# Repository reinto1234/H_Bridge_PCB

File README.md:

# H-Bridge PCB Project

## Project Description
This project involves the design and implementation of an **educational single-phase H-Bridge inverter** controlled by an **Espressif ESP32**.  
The system demonstrates **bipolar sinusoidal PWM (SPWM)** operation with **closed-loop VRMS amplitude control** and a **browser-based interface** for monitoring and control.  
The H-Bridge can drive loads with the following ratings:

- **Input Voltage:** 24 V  
- **Input Current:** up to 10 A  
- **Power:** ≈ 240 W  

### Features
- Fixed **switching frequency:** 35 kHz  
- Fixed **output frequency:** 50 Hz  
- **Bipolar SPWM modulation** (only)  
- **Closed-loop VRMS control** using PI regulation  
- **Web-based UI** (HTTP + WebSocket) for control and telemetry  
- **Input/Output power measurement**  
- **Overcurrent protection** using INA228 (auto driver shutdown + UI fault latch)  

The project consists of two main components:  
1. **H_Bridge_PCB_Design** — KiCad PCB layout and schematic.  
2. **H_Bridge_PCB_Code** — Firmware for the ESP32 controller.

---

## Directory Structure

<h2>Directory Structure</h2>
<pre><code>H_Bridge_PCB_Project/
├── H_Bridge_PCB_Design/        # KiCad design files
├── H_Bridge_PCB_Code/          # ESP32 firmware
│   ├── include/                # Header files
│   │   ├── Controller.h
│   │   ├── I2C.h
│   │   ├── Input_meas.h
│   │   ├── mutexdefinitions.h
│   │   ├── Output_meas.h
│   │   ├── PWM.h
│   │   ├── spi_sampler.h
│   │   ├── Tasks.h
│   │   └── webserver.h
│   │
│   ├── src/                    # Source files
│   │   ├── Controller.cpp
│   │   ├── I2C.cpp
│   │   ├── Input_meas.cpp
│   │   ├── Output_meas.cpp
│   │   ├── PWM.cpp
│   │   ├── spi_sampler.cpp
│   │   ├── Tasks.cpp
│   │   ├── webserver.cpp
│   │   └── main.cpp
│   │
│   ├── data/                   # Webserver files (LittleFS)
│   │   ├── index.html
│   │   ├── script.js
│   │   └── style.css
│
├── lib/                        # Optional local libraries
├── platformio.ini              # PlatformIO configuration
├── images/                     # Flowchart and figures
└── README.md                   # This file
</code></pre>

---

## Requirements

### Hardware:
- PCB based on KiCad design  
- 24 V DC power supply (≥ 10 A)  
- Resistive or inductive load (max ≈ 240 W)  
- Gate drivers with integrated dead-time  
- INA228 current/voltage monitor for input sensing  

### Software:
- [KiCad](https://www.kicad.org/) — PCB design  
- [PlatformIO](https://platformio.org/) — firmware build  
- [VS Code](https://code.visualstudio.com/) — recommended IDE  

---

## Webserver
The ESP32 provides a **built-in Wi-Fi access point** and hosts a **web-based interface** for control and measurement visualization.

### Connect to WLAN Access Point
- **SSID:** `H_Bridge_Control`  
- **Password:** `12345678`

### Open the web interface:
👉 [http://192.168.4.1/](http://192.168.4.1/)

**Functions:**
- Start/Stop the inverter  
- Set VRMS target  
- Display live telemetry (Vin, Iin, VRMS, IRMS, PF, P, Q, f)  
- View and acknowledge overcurrent faults  

---

## Code
The firmware is implemented in **C++** (Arduino / FreeRTOS).  
The web interface is built with **HTML**, **JavaScript**, and **CSS**.

---

### Flowchart

---

## Code Documentation
Brief overview of the most relevant components.

### Inverter Implementation (`PWM.cpp`)
Implements the real-time control of the full-bridge inverter:

- **startInverter()** — Initializes and enables PWM output.  
- **stopInverter()** — Stops PWM and resets inverter state.  
- **generateSPWM()** — Produces bipolar SPWM using a sine table.  
- **begin()** — Configures LEDC channels, frequency, and timers.  
- **getMeasurements()** — Retrieves latest measurement snapshot.  
- **computePI()** — Executes PI algorithm to maintain VRMS target.  
- **loop()** — Runs the inverter control logic at fixed timing intervals.  

### Controller Implementation (`Controller.cpp`)
Implements the PI controller used to regulate the inverter’s RMS output voltage:

- **PIController()** — Initializes PI gains, integrator state, limits, and VRMS target.  
- **ControlRMS()** — Computes RMS error and updates the global Q10 amplitude factor atomically.  
- **compute()** — Executes PI algorithm with anti-windup and output clamping to min/max limits.  
- **g_amp_q10** — Global Q10-formatted amplitude value used by the SPWM stage.  

### I²C Bus Setup (`I2C.cpp`)
Implements the I²C interface for the INA228 current/voltage sensor:

- **I2CINA** — Dedicated I²C bus instance (port 0) used by the input measurement subsystem.  

### Input Measurement (`Input_meas.cpp`)
Implements DC input voltage, current, and power measurement using INA228:

- **init()** — Initializes I²C bus, scans for devices, configures INA228, and sets averaging/timing.  
- **init1()** — Lightweight I²C initialization helper without full sensor setup.  
- **configure_overcurrent_alert_only()** — Configures INA228 alert registers for shunt overcurrent shutdown.  
- **getVoltage()** — Reads and returns the DC input voltage in volts.  
- **getCurrent()** — Reads and returns the shunt current in amperes.  
- **getPower()** — Reads and returns the input power in watts with simple error rejection.  
- **measurementall()** — Updates the shared input measurement buffer (voltage, current, power) in a mutex-protected way and returns it.  
- **scanI2C()** — Scans the I²C bus, prints found devices, and restarts the bus if no device is detected.  

### Main Application (`main.cpp`)
Implements system bring-up and FreeRTOS task orchestration:

- **setup()** — Initializes serial logging, mutexes, input measurement, Wi-Fi AP, webserver, SPI measurement engines, safety pins, and the overcurrent interrupt; then creates all application tasks.  
- **loop()** — Empty main loop; periodically yields since all logic is implemented in FreeRTOS tasks.  
- **Task handles** — Stores references to sampler, analyzer, WebSocket, controller, printer, and emergency stop tasks for debugging/management.  

### Mutex Definitions (`mutexdefinitions.cpp`)
Implements globally shared FreeRTOS mutexes for synchronization:

- **inverterMutex** — Protects access to the inverter state and control functions.  
- **measurementinMutex** — Protects shared input measurement buffer.  
- **measurementoutMutex** — Protects shared output measurement structures.  
- **measurementSpiMutex** — Protects SPI-related measurement buffers and state.  

### Output Measurement (`Output_meas.cpp`)
Implements decimation, CIC filtering, RMS, and frequency analysis for AMC1306 bitstreams:

- **buildByteCicLut()** — Precomputes CIC integrator/differentiator contributions for all 8-bit patterns.  
- **OutputMeasurements()** — Configures OSR, full-scale voltage, buffer sizes, and initial bit rate.  
- **init()** — Allocates decimation ring buffers, analysis windows, and period buffers (with PSRAM support) and creates a snapshot mutex.  
- **copyRecentWindowWithStats()** — Copies the newest segment from the decimation ring and computes mean, min, and max.  
- **findLastTwoRisingZcHyst()** — Detects the last two rising zero-crossings with hysteresis to define one AC period.  
- **computeRmsOnePeriodExact()** — Computes exact RMS over one period using piecewise linear interpolation.  
- **processRxBytesAndUpdateBitrate()** — Processes raw SPI bytes, runs CIC pipeline, generates decimated voltage samples, and updates effective bit rate.  
- **analyzeStep()** — Centers the signal, finds period boundaries, computes frequency, extracts a centered period, and calculates RMS.  
- **getSnapshot()** — Returns the latest snapshot (RMS, frequency, period length) in a thread-safe way.  
- **copyLastPeriod()** — Copies the last detected waveform period into a caller-provided buffer.  
- **copySinceSeq32()** — Provides incremental decimated samples since a given sequence index, for streaming or plotting.  

### Emergency Stop (`safety.cpp`)
Implements minimal emergency-stop signaling for overcurrent events:

- **g_emergency_stop** — Global volatile flag indicating an active emergency stop condition.  
- **onAlertISR()** — ISR that sets the emergency stop flag when the INA228 alert pin fires.  

### SPI Sampler (`spi_sampler.cpp`)
Implements DMA-driven SPI acquisition for dual AMC1306 isolated ADC channels:

- **g_ch1_om / g_ch2_om** — OutputMeasurements instances for both channels with hardware-specific scaling.  
- **g_sampler1 / g_sampler2** — Sampler context structures for SPI hosts, pins, DMA channels, and transactions.  
- **g_pack1 / g_pack2** — Pairs of sampler context and OutputMeasurements used by sampler tasks.  
- **spiSamplerInitMeasurements()** — Initializes both OutputMeasurements engines and validates buffer allocation.  
- **spiInitAndStart()** — Allocates DMA buffers, configures SPI bus and device, prepares transactions, and seeds the transaction queue.  

### Task Scheduler (`Tasks.cpp`)
Implements all FreeRTOS tasks for sampling, analysis, UI updates, control, and safety:

- **spiSamplerTask()** — Retrieves completed SPI DMA transactions, feeds data into OutputMeasurements, requeues transactions, and maintains sampling timing.  
- **analyzerTask()** — Periodically calls analyzeStep() on a given OutputMeasurements instance to update RMS and frequency.  
- **printerTask()** — Periodically prints analyzer timing, latest period samples, RMS, and frequency for both channels over serial.  
- **webSocketTask()** — Processes WebSocket events in a loop to keep client connections responsive.  
- **webSocketUpdate()** — Periodically collects input and output measurements and sends them as JSON via WebSocket to the UI.  
- **ControllerTask()** — Runs the VRMS control loop by feeding the measured RMS value into the PI controller of the inverter.  
- **EmergencyStopTask()** — Monitors the global emergency-stop flag, stops the inverter, signals the E-STOP output, and notifies the web UI when overcurrent is detected.  

### Webserver (`webserver.cpp`)
Implements Wi-Fi access point, HTTP endpoints, and WebSocket telemetry/UI control:

- **resetDefaults()** — Resets VRMS target and running state to their default values.  
- **initWiFi()** — Starts the Wi-Fi SoftAP for the H-Bridge control interface.  
- **initServer()** — Mounts LittleFS, serves static `/index.html`, `/style.css`, `/script.js`, and defines `/start`, `/stop`, and `/ack-trip` endpoints.  
- **updateMeasurements()** — Packs input/output data and frequency into JSON and broadcasts it over WebSocket.  
- **broadcastStatus()** — Sends current inverter running state to all connected clients via WebSocket.  
- **onWebSocketEvent()** — Handles client connect/disconnect events and sends initial status on connect.  
- **broadcastTrip()** — Notifies all clients of a trip condition and updates running state.  
- **_VRMS / _isRunning** — Static internal state for desired RMS value and inverter run/stop status.  

**HTTP Endpoints:**
- `/` – Main HTML page  
- `/start` – Start inverter  
- `/stop` – Stop inverter  
- `/update` – Update VRMS target  
- `/bipolar.png` – Waveform reference  

---

## Overcurrent Protection
Overcurrent protection is implemented through the **INA228** fault pin:  
1. When a current threshold is exceeded, **drivers are disabled immediately**.  
2. A **fault message** is sent to the web interface.  
3. After user acknowledgment, the inverter can be restarted safely.  

---

## Safety  
- Use **current-limited** power supplies during development.  
- Verify **MOSFET temperature and load** ratings.  
- For **educational/laboratory use only**.

---

## License
Released for **educational and research purposes**.  
Use responsibly.

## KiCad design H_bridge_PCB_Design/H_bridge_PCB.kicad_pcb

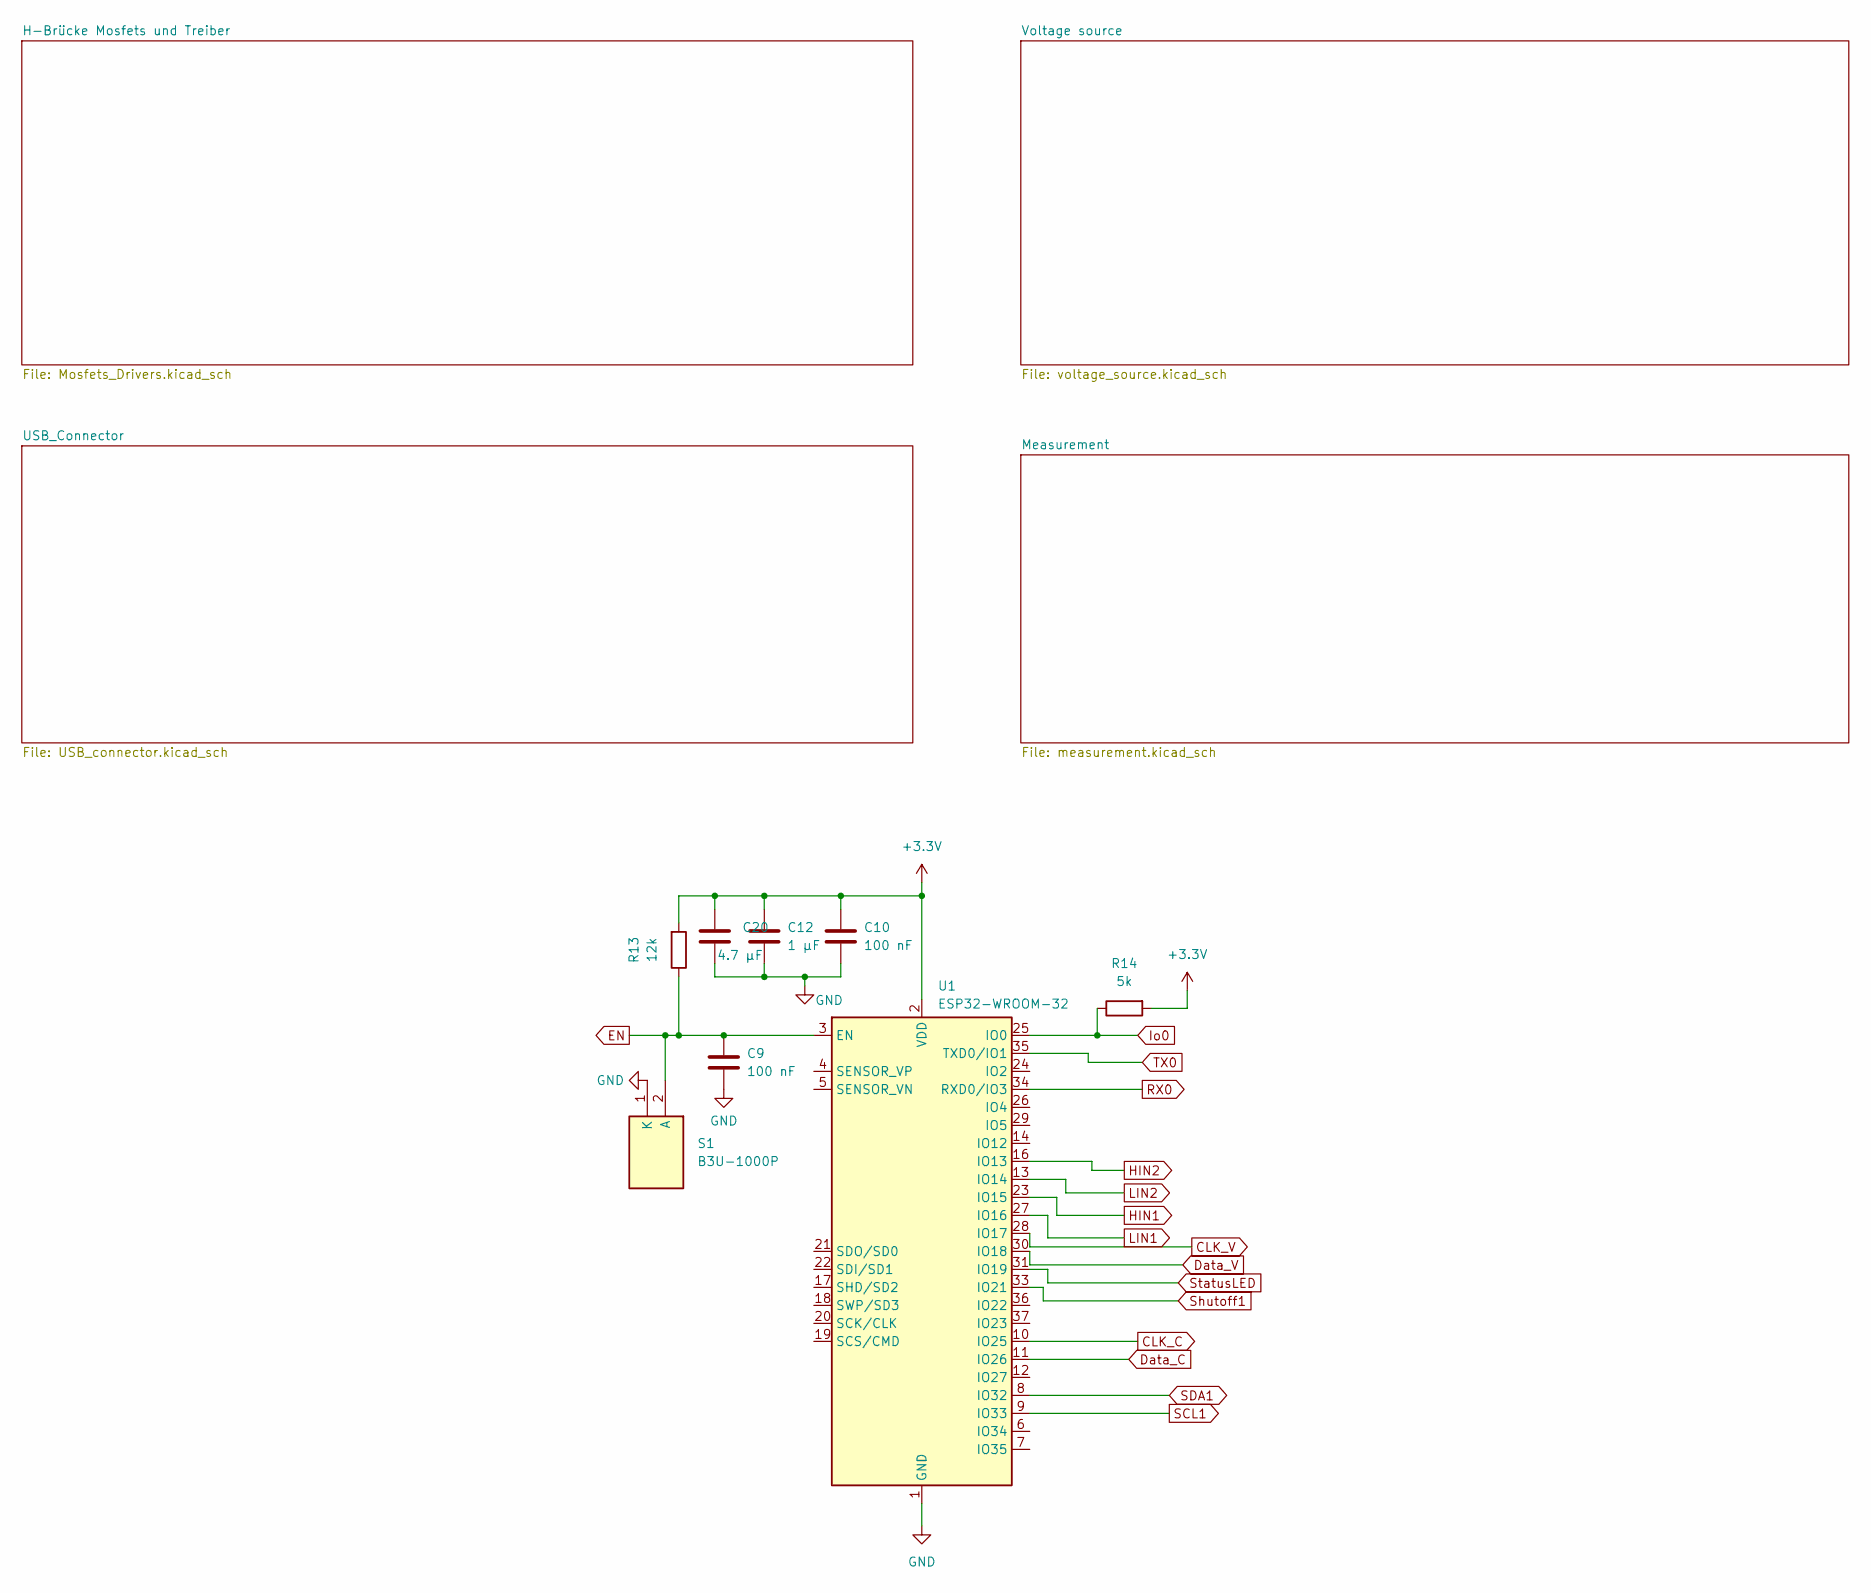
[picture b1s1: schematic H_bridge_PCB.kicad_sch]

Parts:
C9, C10: 100 nF; R_0805_2012Metric_Pad1.20x1.40mm_HandSolder; LCSC Part # C49678
C12: 1 µF; R_0805_2012Metric_Pad1.20x1.40mm_HandSolder; LCSC Part # C28323
C20: 4.7 µF; R_0805_2012Metric_Pad1.20x1.40mm_HandSolder; LCSC Part # C49678
R13: 12k; R_0805_2012Metric_Pad1.20x1.40mm_HandSolder; LCSC Part # C139925
R14: 5k; R_0805_2012Metric_Pad1.20x1.40mm_HandSolder; LCSC Part # C2828700
S1: B3U-1000P; Manufacturer_Part_Number B3U-1000P; Mouser Part Number 653-B3U-1000P
U1: ESP32-WROOM-32; LCSC Part # C701343

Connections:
+3.3V: C10.1, C12.1, C20.1, R13.2, R14.2, U1.2 (VDD); also elsewhere on the board
CLK_C: U1.10 (IO25); also elsewhere on the board
CLK_V: U1.28 (IO17); also elsewhere on the board
Data_C: U1.11 (IO26); also elsewhere on the board
Data_V: U1.30 (IO18); also elsewhere on the board
EN: C9.1, R13.1, S1.2 (A), U1.3 (EN); also elsewhere on the board
GND: C9.2, C10.2, C12.2, C20.2, S1.1 (K), U1.1 (GND), U1.15 (GND), U1.38 (GND), U1.39 (GND); also elsewhere on the board
HIN1: U1.23 (IO15); also elsewhere on the board
HIN2: U1.16 (IO13); also elsewhere on the board
Io0: R14.1, U1.25 (IO0); also elsewhere on the board
LIN1: U1.27 (IO16); also elsewhere on the board
LIN2: U1.13 (IO14); also elsewhere on the board
RX0: U1.34 (RXD0/IO3); also elsewhere on the board
SCL1: U1.9 (IO33); also elsewhere on the board
SDA1: U1.8 (IO32); also elsewhere on the board
Shutoff1: U1.33 (IO21); also elsewhere on the board
StatusLED: U1.31 (IO19)
TX0: U1.35 (TXD0/IO1); also elsewhere on the board

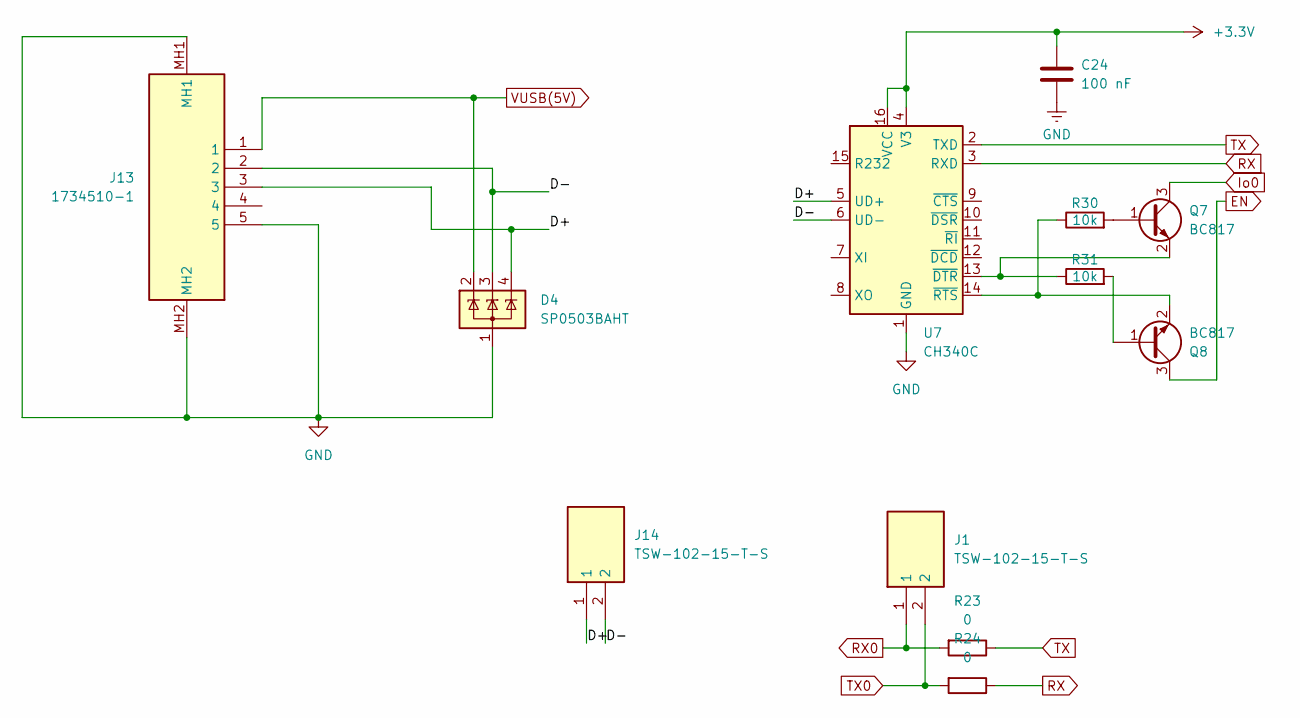
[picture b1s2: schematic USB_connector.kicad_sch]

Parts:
C24: 100 nF; R_0805_2012Metric_Pad1.20x1.40mm_HandSolder; LCSC Part # C49678
D4: SP0503BAHT; SOT-143; LCSC Part # C7074
J1, J14: TSW-102-15-T-S; TSW-102-XX-YY-S; Mouser Part Number 200-TSW10215TS
J13: 1734510-1; 17345101; Mouser Part Number 571-1734510-1
Q7, Q8: BC817; SOT-23_Handsoldering; LCSC Part # C475629
R23, R24: 0; R_0805_2012Metric_Pad1.20x1.40mm_HandSolder; LCSC Part # C2074219
R30, R31: 10k; R_0805_2012Metric_Pad1.20x1.40mm_HandSolder; LCSC Part # C84376
U7: CH340C; SOIC-16_3.9x9.9mm_P1.27mm; LCSC Part # C84681

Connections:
+3.3V: C24.1, U7.4 (V3), U7.16 (VCC); also elsewhere on the board
/USB_Connector/D+: D4.4 (K), J13.3, J14.1, U7.5 (UD+)
/USB_Connector/D-: D4.3 (K), J13.2, J14.2, U7.6 (UD-)
EN: Q8.3 (C); also elsewhere on the board
GND: C24.2, D4.1 (A), J13.5, J13.MH1, J13.MH2, U7.1 (GND); also elsewhere on the board
Io0: Q7.3 (C); also elsewhere on the board
unnamed: Q7.1 (B), R30.2
unnamed: Q7.2 (E), R31.1, U7.13 (~DTR)
unnamed: Q8.1 (B), R31.2
unnamed: Q8.2 (E), R30.1, U7.14 (~RTS)
RX: R24.1, U7.3 (RXD)
RX0: J1.1, R23.2; also elsewhere on the board
TX: R23.1, U7.2 (TXD)
TX0: J1.2, R24.2; also elsewhere on the board
VUSB(5V): D4.2 (K), J13.1; also elsewhere on the board

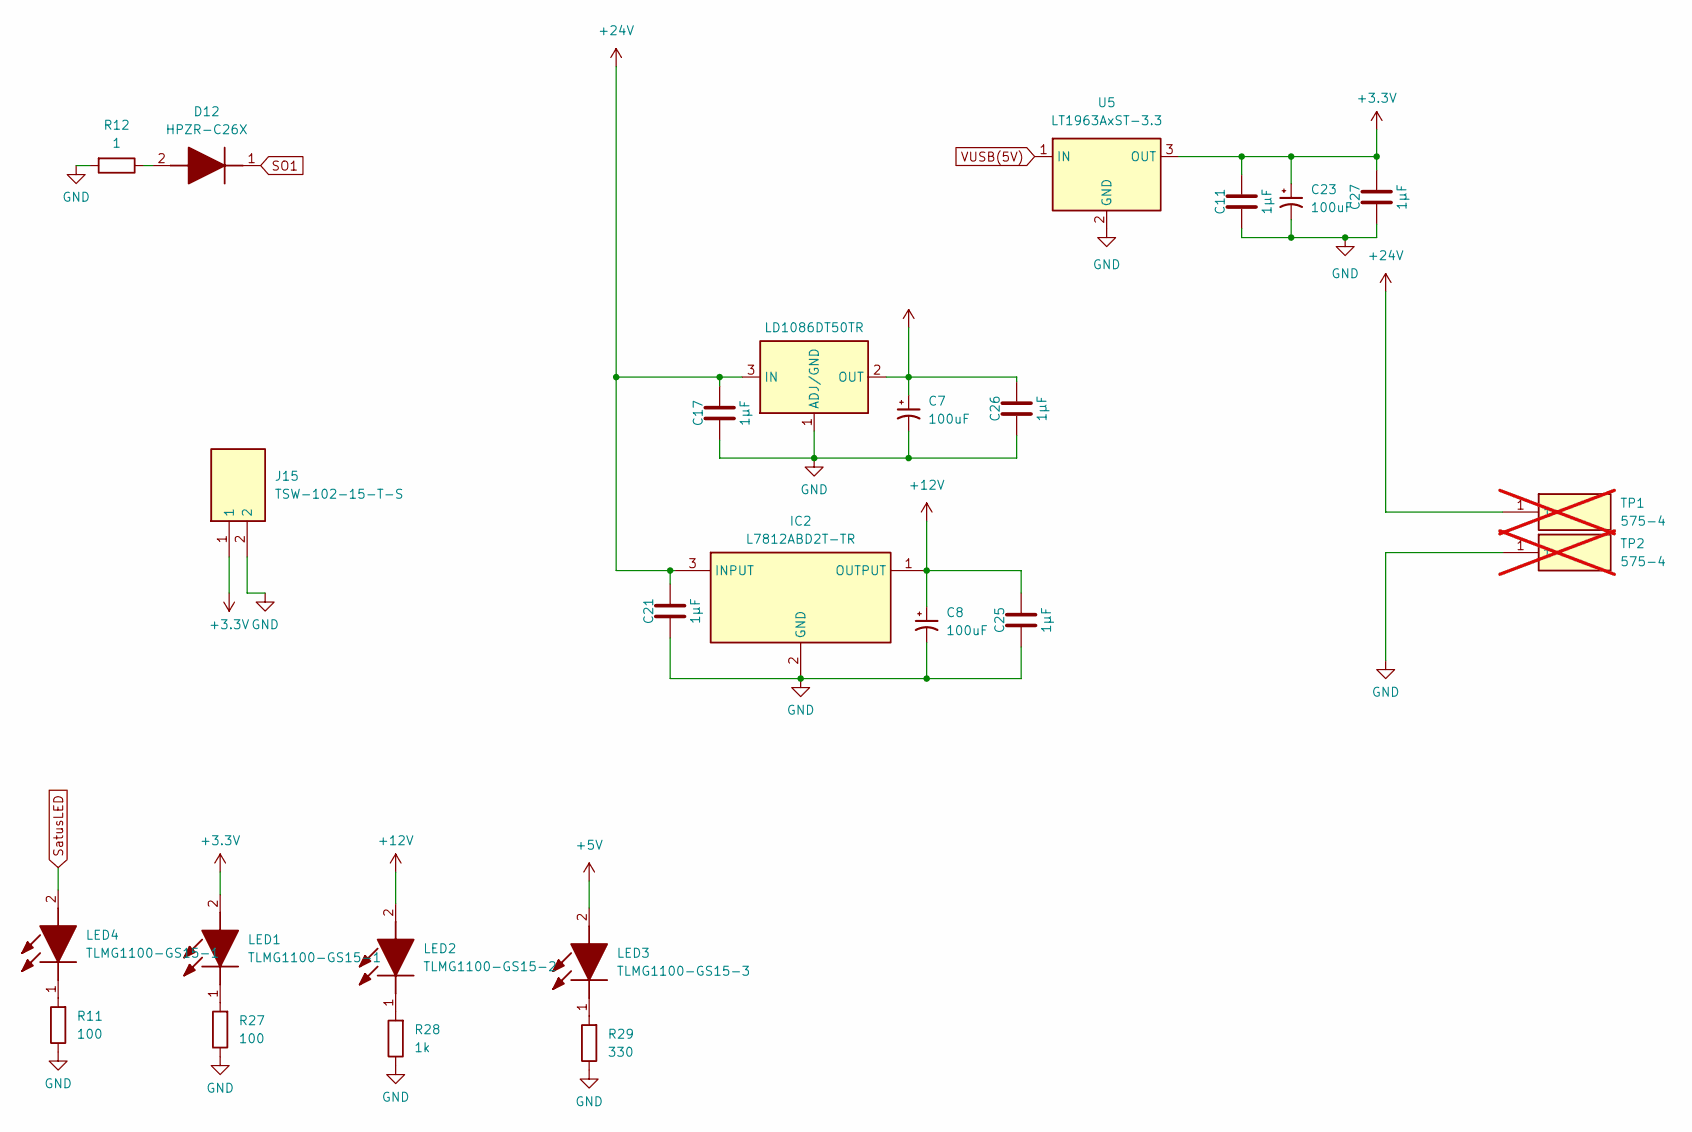
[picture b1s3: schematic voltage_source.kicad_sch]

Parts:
C7, C8, C23: 100uF; EEE1AA101SP; LCSC Part # C128464
C11, C17, C21, C25, C26, C27: 1µF; R_0805_2012Metric_Pad1.20x1.40mm_HandSolder; LCSC Part # C28323
D12: HPZR-C26X; HPZRC26X; Manufacturer_Part_Number HPZR-C26X
IC2: L7812ABD2T-TR; L7812ABD2TTR; Manufacturer_Part_Number L7812ABD2T-TR; Mouser Part Number 511-L7812ABD2T-TR
J15: TSW-102-15-T-S; TSW-102-XX-YY-S; Mouser Part Number 200-TSW10215TS
LED1, LED4: TLMG1100-GS15-1; R_0805_2012Metric_Pad1.20x1.40mm_HandSolder; Mouser Part Number 78-TLMG1100-GS15
LED2: TLMG1100-GS15-2; R_0805_2012Metric_Pad1.20x1.40mm_HandSolder; Mouser Part Number 78-TLMG1100-GS15
LED3: TLMG1100-GS15-3; R_0805_2012Metric_Pad1.20x1.40mm_HandSolder; Mouser Part Number 78-TLMG1100-GS15
R11, R27: 100; R_0805_2012Metric_Pad1.20x1.40mm_HandSolder; LCSC Part # C115423
R12: 1; R_0805_2012Metric_Pad1.20x1.40mm_HandSolder; LCSC Part # C4129769
R28: 1k; R_0805_2012Metric_Pad1.20x1.40mm_HandSolder; LCSC Part # C95781
R29: 330; R_0805_2012Metric_Pad1.20x1.40mm_HandSolder; LCSC Part # C4129769
TP1, TP2: 575-4; 5754; Mouser Part Number 534-575-4; not fitted
U5: LT1963AxST-3.3; SOT-223-3_TabPin2; LCSC Part # C459918
U6: LD1086DT50TR; TO-252-2; LCSC Part # C164853

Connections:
+3.3V: C11.1, C23.1, C27.1, J15.1, LED1.2 (A), U5.3 (OUT); also elsewhere on the board
+5V: C7.1, C26.1, LED3.2 (A), U6.2 (OUT); also elsewhere on the board
+12V: C8.1, C25.1, IC2.1 (OUTPUT), LED2.2 (A); also elsewhere on the board
GND: C7.2, C8.2, C11.2, C17.2, C21.2, C23.2, C25.2, C26.2, C27.2, IC2.2 (GND), J15.2, R11.1, R12.2, R27.1, R28.1, R29.1, TP2.1, U5.2 (GND), U6.1 (ADJ/GND); also elsewhere on the board
unnamed: D12.2 (A), R12.1
unnamed: LED1.1 (K), R27.2
unnamed: LED2.1 (K), R28.2
unnamed: LED3.1 (K), R29.2
unnamed: LED4.1 (K), R11.2
SO1: D12.1 (K); also elsewhere on the board
SatusLED: LED4.2 (A)
VUSB(5V): U5.1 (IN); also elsewhere on the board

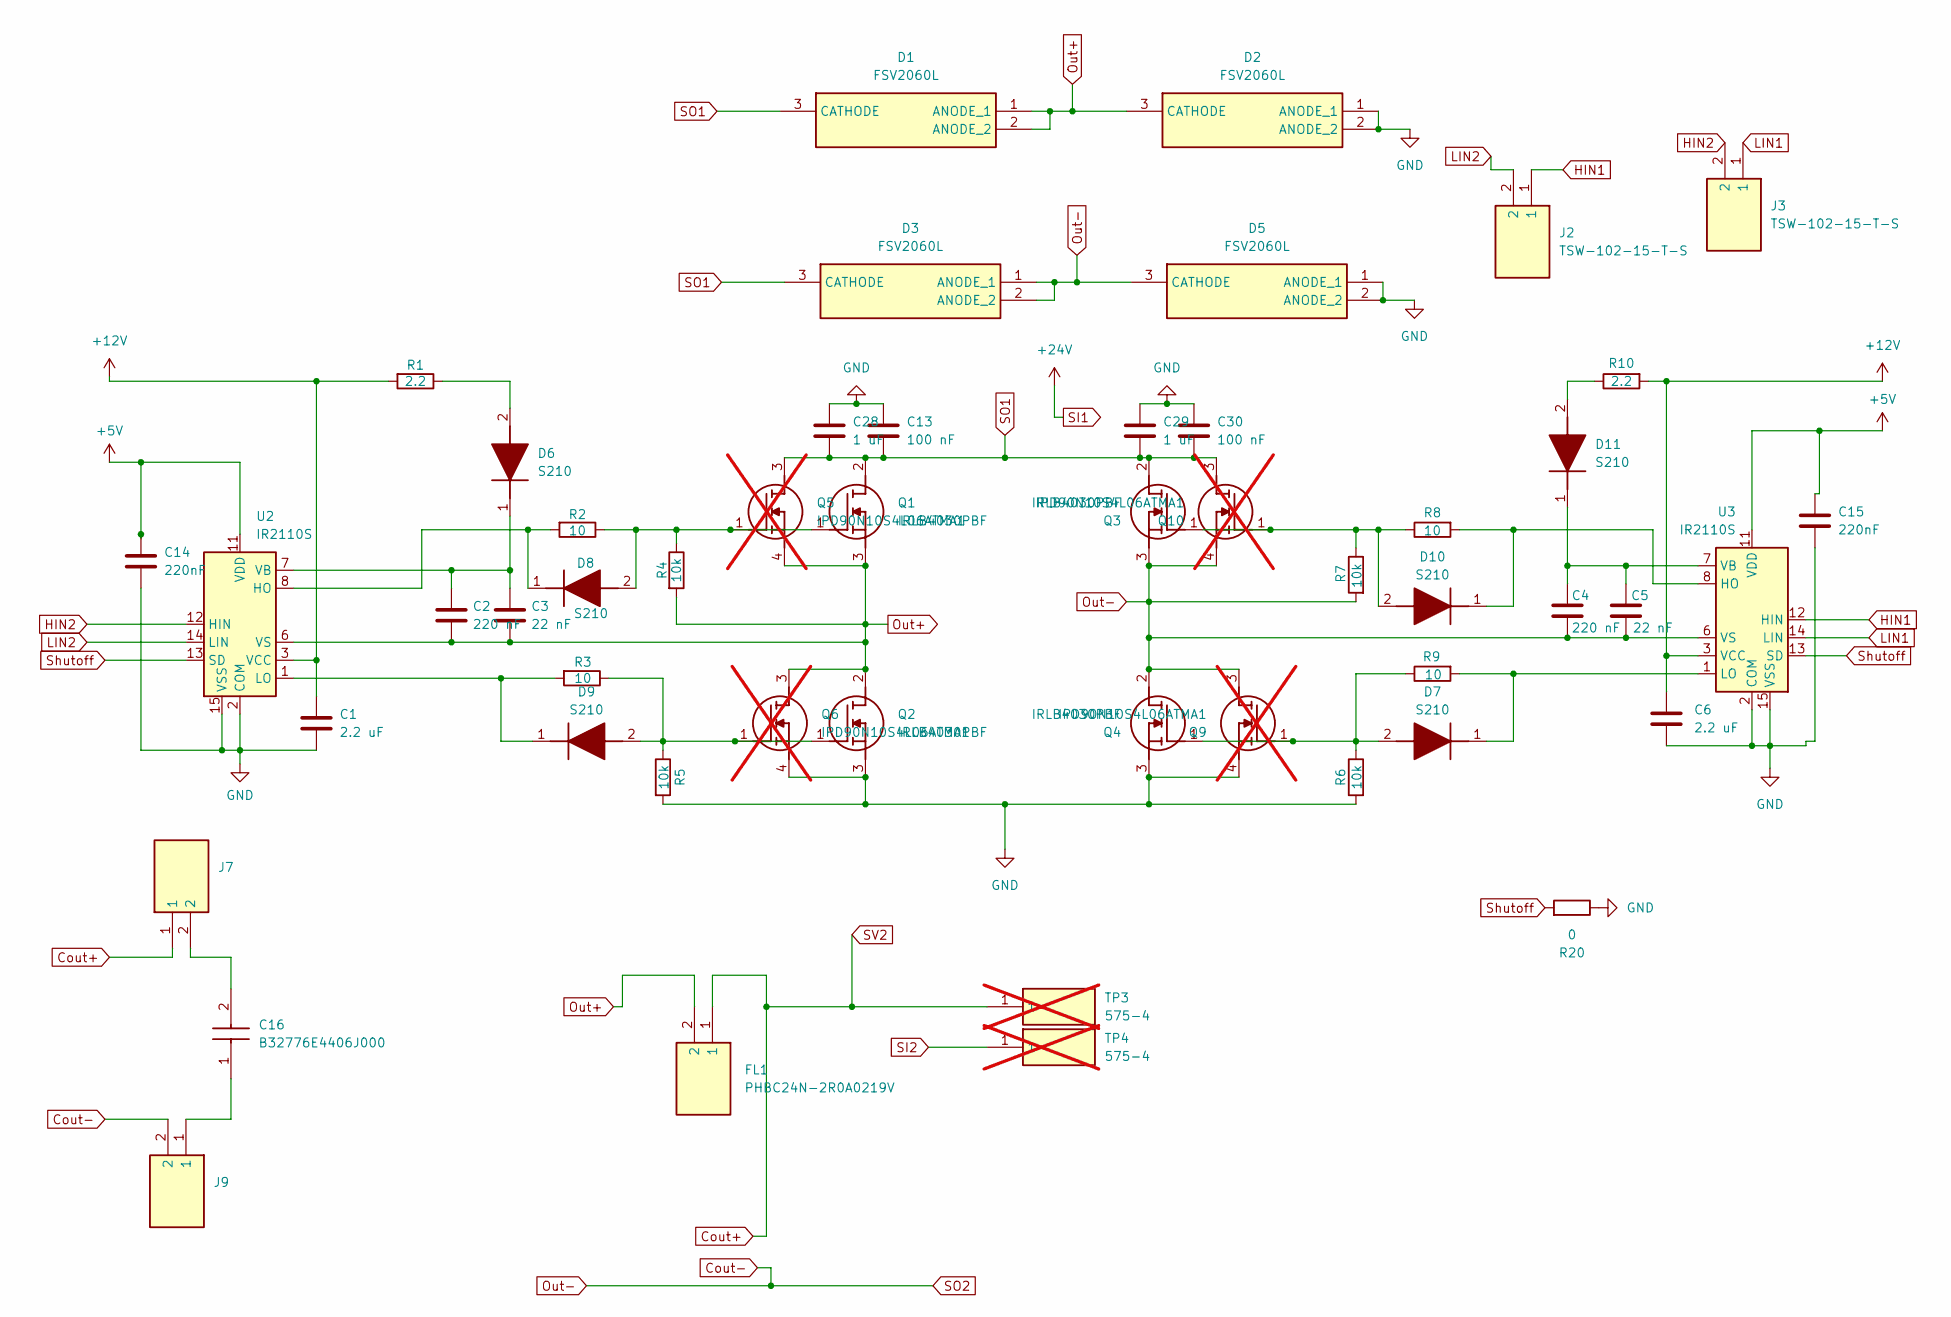
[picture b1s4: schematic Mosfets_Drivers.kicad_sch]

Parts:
C1, C6: 2.2 uF; R_0805_2012Metric_Pad1.20x1.40mm_HandSolder; LCSC Part # C513763
C2, C4: 220 nF; R_0805_2012Metric_Pad1.20x1.40mm_HandSolder; LCSC Part # C354366
C3, C5: 22 nF; R_0805_2012Metric_Pad1.20x1.40mm_HandSolder; LCSC Part # C2181592
C13, C30: 100 nF; R_0805_2012Metric_Pad1.20x1.40mm_HandSolder; LCSC Part # C49678
C14, C15: 220nF; R_0805_2012Metric_Pad1.20x1.40mm_HandSolder; LCSC Part # C354366
C16: B32776E4406J000; Mouser Part Number 871-B32776E4406J000
C28, C29: 1 uF; R_0805_2012Metric_Pad1.20x1.40mm_HandSolder; LCSC Part # C28323
D1, D2, D3, D5: FSV2060L; Mouser Part Number 512-FSV2060L
D6, D7, D8, D9, D10, D11: S210; DIOM5336X265N; Manufacturer_Part_Number S210; Mouser Part Number 512-S210
FL1: PHBC24N-2R0A0219V; PHBC24N2R0A0219V; Mouser Part Number 80-PHBC24N-2R0A0219V
J2, J3, J7, J9: TSW-102-15-T-S; TSW-102-XX-YY-S; Mouser Part Number 200-TSW10215TS
Q1, Q2, Q3, Q4: IRLB4030PBF; TO254P483X1016X1994-3P; Mouser Part Number 942-IRLB4030PBF
Q5, Q6, Q9, Q10: IPD90N10S4L06ATMA1; Mouser Part Number 726-IPD90N10S4L06ATM; not fitted
R1, R10: 2.2; R_0805_2012Metric_Pad1.20x1.40mm_HandSolder; LCSC Part # C25301
R2, R3, R8, R9: 10; R_0805_2012Metric_Pad1.20x1.40mm_HandSolder; LCSC Part # C3016584
R4, R5, R6, R7: 10k; R_0805_2012Metric_Pad1.20x1.40mm_HandSolder; LCSC Part # C84376
R20: 0; R_0805_2012Metric_Pad1.20x1.40mm_HandSolder; LCSC Part # C2074219
TP3, TP4: 575-4; 5754; Mouser Part Number 534-575-4; not fitted
U2, U3: IR2110S; SOIC-16W_7.5x10.3mm_P1.27mm; LCSC Part # C2968

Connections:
+5V: C14.1, C15.1, U2.11 (VDD), U3.11 (VDD); also elsewhere on the board
+12V: C1.1, C6.1, R1.2, R10.2, U2.3 (VCC), U3.3 (VCC); also elsewhere on the board
Cout+: FL1.1, J7.1, TP3.1; also elsewhere on the board
Cout-: C4.2, C5.2, D3.1 (ANODE_1), D3.2 (ANODE_2), D5.3 (CATHODE), J9.2, Q3.3 (S), Q4.2 (D), Q9.3 (D), Q10.4 (S), R7.2, U3.6 (VS); also elsewhere on the board
GND: C1.2, C6.2, C13.2, C14.2, C15.2, C28.2, C29.2, C30.2, D2.1 (ANODE_1), D2.2 (ANODE_2), D5.1 (ANODE_1), D5.2 (ANODE_2), Q2.3 (S), Q4.3 (S), Q6.4 (S), Q9.4 (S), R5.2, R6.2, R20.1, U2.2 (COM), U2.15 (VSS), U3.2 (COM), U3.15 (VSS); also elsewhere on the board
HIN1: J2.1, U3.12 (HIN); also elsewhere on the board
HIN2: J3.2, U2.12 (HIN); also elsewhere on the board
LIN1: J3.1, U3.14 (LIN); also elsewhere on the board
LIN2: J2.2, U2.14 (LIN); also elsewhere on the board
unnamed: C16.1, J9.1
unnamed: C16.2, J7.2
unnamed: D6.2 (A), R1.1
unnamed: C2.1, C3.1, D6.1 (K), U2.7 (VB)
unnamed: D7.2 (A), Q4.1 (G), Q9.1 (G), R6.1, R9.1
unnamed: D7.1 (K), R9.2, U3.1 (LO)
unnamed: D8.2 (A), Q1.1 (G), Q5.1 (G), R2.1, R4.1
unnamed: D8.1 (K), R2.2, U2.8 (HO)
unnamed: D9.2 (A), Q2.1 (G), Q6.1 (G), R3.1, R5.1
unnamed: D9.1 (K), R3.2, U2.1 (LO)
unnamed: D10.2 (A), Q3.1 (G), Q10.1 (G), R7.1, R8.1
unnamed: D10.1 (K), R8.2, U3.8 (HO)
unnamed: D11.2 (A), R10.1
unnamed: C4.1, C5.1, D11.1 (K), U3.7 (VB)
Out+: C2.2, C3.2, D1.1 (ANODE_1), D1.2 (ANODE_2), D2.3 (CATHODE), FL1.2, Q1.3 (S), Q2.2 (D), Q5.4 (S), Q6.3 (D), R4.2, U2.6 (VS)
SI2: TP4.1; also elsewhere on the board
SO1: C13.1, C28.1, C29.1, C30.1, D1.3 (CATHODE), D3.3 (CATHODE), Q1.2 (D), Q3.2 (D), Q5.3 (D), Q10.3 (D); also elsewhere on the board
Shutoff: R20.2, U2.13 (SD), U3.13 (SD); also elsewhere on the board

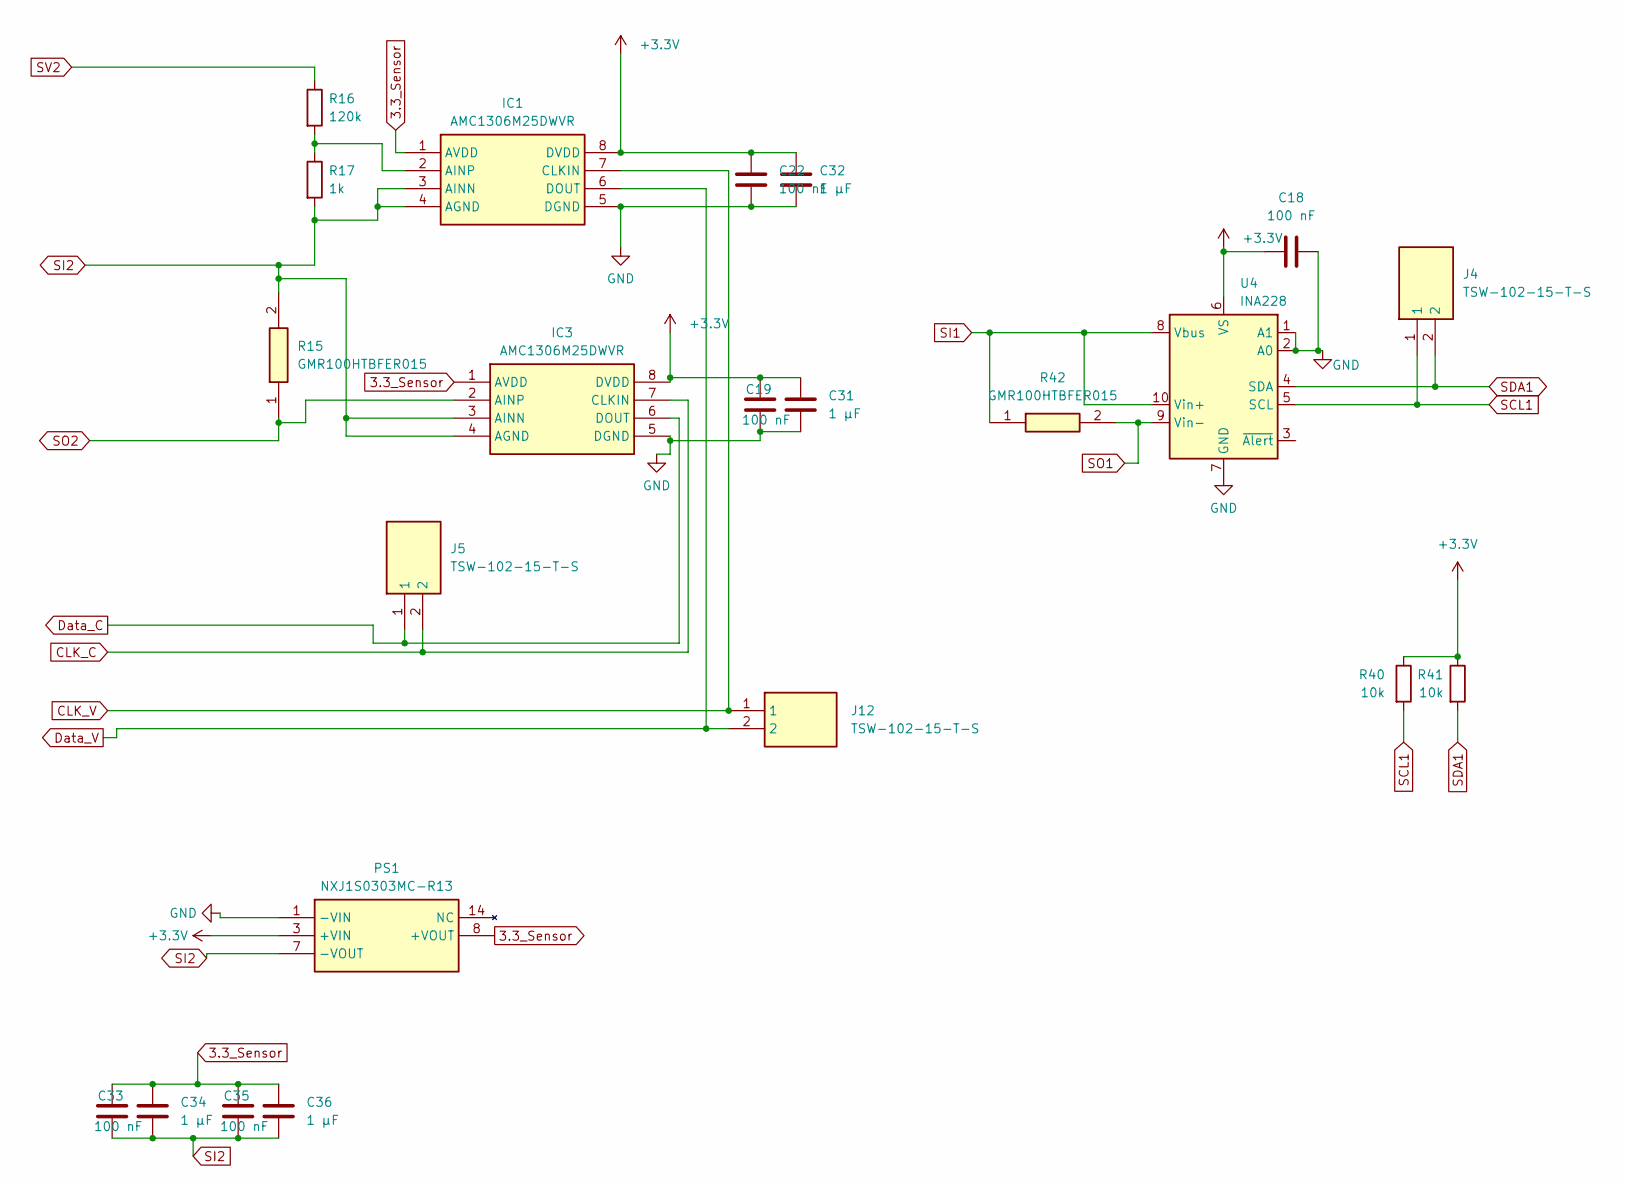
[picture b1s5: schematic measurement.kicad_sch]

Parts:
C18, C19, C22, C33, C35: 100 nF; R_0805_2012Metric_Pad1.20x1.40mm_HandSolder; LCSC Part# C49678
C31, C32, C34, C36: 1 µF; R_0805_2012Metric_Pad1.20x1.40mm_HandSolder; LCSC Part# C49678
IC1, IC3: AMC1306M25DWVR; SOIC127P1150X280-8N; Mouser Part Number 595-AMC1306M25DWVR
J4, J5, J12: TSW-102-15-T-S; TSW-102-XX-YY-S; Mouser Part Number 200-TSW10215TS
PS1: NXJ1S0303MC-R13; NXJ1S0303MCR13; Mouser Part Number 580-NXJ1S0303MC-R13
R15, R42: GMR100HTBFER015; R_2512_6332Metric_Pad1.40x3.35mm_HandSolder; Mouser Part Number 755-GMR100HTBFER015
R16: 120k; R_0805_2012Metric_Pad1.20x1.40mm_HandSolder; LCSC Part# C84376
R17: 1k; R_0805_2012Metric_Pad1.20x1.40mm_HandSolder; LCSC Part# C84376
R40, R41: 10k; R_0805_2012Metric_Pad1.20x1.40mm_HandSolder; LCSC Part# C84376
U4: INA228; VSSOP-10_3x3mm_P0.5mm; LCSC Part# C2862904

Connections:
3.3_Sensor: C33.2, C34.2, C35.2, C36.2, IC1.1 (AVDD), IC3.1 (AVDD), PS1.8 (+VOUT)
+3.3V: C18.1, C19.2, C22.2, C31.2, C32.2, IC1.8 (DVDD), IC3.8 (DVDD), PS1.3 (+VIN), R40.1, R41.1, U4.6 (VS); also elsewhere on the board
CLK_C: IC3.7 (CLKIN), J5.2; also elsewhere on the board
CLK_V: IC1.7 (CLKIN), J12.1; also elsewhere on the board
Cout+: R16.1; also elsewhere on the board
Cout-: IC3.2 (AINP), R15.1; also elsewhere on the board
Data_C: IC3.6 (DOUT), J5.1; also elsewhere on the board
Data_V: IC1.6 (DOUT), J12.2; also elsewhere on the board
GND: C18.2, C19.1, C22.1, C31.1, C32.1, IC1.5 (DGND), IC3.5 (DGND), PS1.1 (-VIN), U4.1 (A1), U4.2 (A0), U4.7 (GND); also elsewhere on the board
unnamed: IC1.2 (AINP), R16.2, R17.1
SCL1: J4.1, R40.2, U4.5 (SCL); also elsewhere on the board
SDA1: J4.2, R41.2, U4.4 (SDA); also elsewhere on the board
SI2: C33.1, C34.1, C35.1, C36.1, IC1.3 (AINN), IC1.4 (AGND), IC3.3 (AINN), IC3.4 (AGND), PS1.7 (-VOUT), R15.2, R17.2; also elsewhere on the board
SO1: R42.2, U4.9 (Vin-); also elsewhere on the board
Shutoff1: U4.3 (~Alert); also elsewhere on the board

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
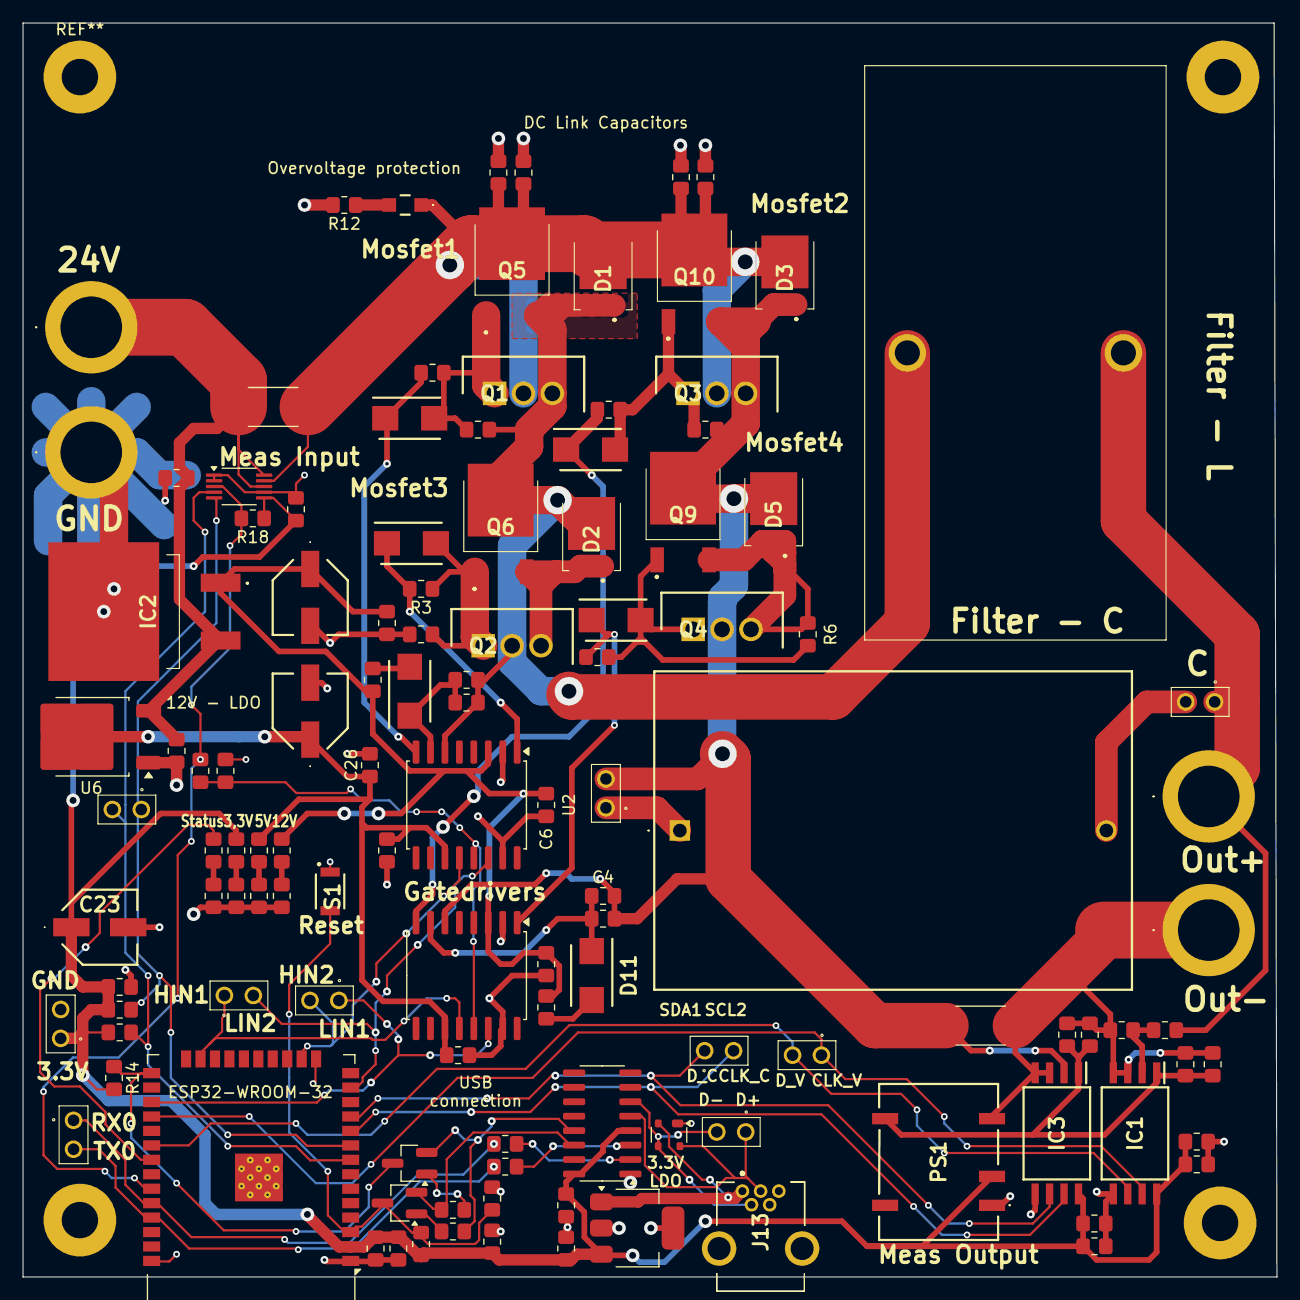
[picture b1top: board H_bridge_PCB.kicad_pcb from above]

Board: 2 copper layers, 110.2 x 110.2 mm, 120 parts (0 on the bottom side), 56 nets.

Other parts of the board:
R18: 12k; R_0805_2012Metric_Pad1.20x1.40mm_HandSolder
R19: 0; R_0805_2012Metric_Pad1.20x1.40mm_HandSolder

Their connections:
+3.3V: R18.1; also elsewhere on the board
Shutoff: R19.1; also elsewhere on the board
Shutoff1: R18.2, R19.2; also elsewhere on the board

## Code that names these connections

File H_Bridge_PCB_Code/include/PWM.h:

/*************************************************************************
 * @file PWM.h
 * @date 2025/01/31
 *
 ************************************************************************/

#ifndef PWM_H
#define PWM_H

/*************************************************************************
 * Includes
 ************************************************************************/
#include <Arduino.h>
#include <math.h>
#include <iostream>
#include <vector>
#include "Controller.h"

/*************************************************************************
 * Defines
 ************************************************************************/
// GPIO-Pins für H-Brücke
#define HIN1 15
#define LIN1 16
#define HIN2 13
#define LIN2 14

// PWM-Konfiguration
#define PWM_CHANNEL_1 0
#define PWM_CHANNEL_2 1
#define RESOLUTION 10  // 10-Bit PWM
//#define CYCLETIME_PWM 0.5  //PWM-Zykluszeit in ms

// Sinus-Tabelle für SPWM
#define OUTPUT_FREQ 50   // Ausgangsfrequenz in Hz
#define SINE_STEPS 200 // Anzahl der Schritte in der Sinus-Tabelle


#define TIMER_INTERVAL_US (1000000 / (OUTPUT_FREQ * SINE_STEPS))
#define S_FREQ 35000    // Schaltfrequenz in Hz (35 kHz)




/*************************************************************************
 * Class
 ************************************************************************/
class HBridgeInverter {
public:
    HBridgeInverter(float vrms);
    void begin();
    void generateSPWM();
    PIController controller; // Example gains and output limits

private:
    
    int16_t sineTable[SINE_STEPS];
    float pwmDutyCycle;
    uint16_t stepIndex;
    float measurementBuffer[10];
    intr_handle_t spwmIntrHandle;
    
};

void startInverter(float vrms);
void stopInverter();

// Declare global inverter instance so other files can use it
extern HBridgeInverter* inverter;

#endif // PWM_H
